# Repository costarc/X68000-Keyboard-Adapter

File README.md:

# X68000 PS/2 Keyboard Adapter (GKA-AT68)

A small adapter that lets a standard PS/2 keyboard drive a Sharp X68000. A PIC16F84 reads the
PS/2 keyboard, translates the scan codes and talks to the X68000 over its 2400 baud keyboard link.

## Repository layout

| Path | What it is |
|---|---|
| `GKA-AT68 Ver1.65 source code (for MPASM).zip` | Original firmware source (PIC assembly, `gkaat68.asm`), Ver1.65 |
| `GKA-AT68 firmware Ver1.65 (INHX8M format for PIC16F84)/` | Original, known-good firmware image (`at68v165.hex`) |
| `GKA-AT68 Assembly Instructions.pdf`, `GKA-AT68 Schematics.png` | Build instructions and schematic |
| `Kicad/` | PCB design (KiCad), fabrication files and interactive BOM |
| `GKA-AT68-C/` | **New:** the firmware rewritten in C for MPLAB X + XC8 (see below) |

## GKA-AT68-C: the C version of the firmware

### Why
The original assembly works, but it is hard to read and hard to change: timing, protocol handling and
key tables are interleaved in one 1,500-line file written for MPASM. The C version exists to give
a firmware that is

- **easier to understand**: one small file per job (PS/2 receive, X68000 UART, key map, main loop);
- **easier to modify**: users can remap keys, change timing or add features without touching assembly;
- **built with a modern toolset**: MPLAB X and the free-mode XC8 compiler (developed with XC8 v2.46).

The assembly version stays in the repository as the reference and the proven firmware. **Its hex is
untouched.** The C version is newer and has been verified by simulation and a compile only, not yet on
hardware (see Status).

### Origin
It is a port of `gkaat68.asm` Ver1.65, not a new design. Kept from the original:

- the hardware and pin roles (PIC16F84 at 9.8304 MHz, PS/2 on RA0-RA3, X68000 link on RB0/RB1/RB3);
- the architecture: a **Timer0 interrupt every ~52 us (1/8 of a 2400 baud bit)** runs a software UART
  for both transmit and receive, with an 8-byte receive FIFO;
- the Timer0 setup and reload constant (`256 - 64 + 3`, prescaler 1:2);
- the PS/2 set-2 to X68000 key tables, transcribed from the assembly.

### Architecture (`GKA-AT68-C/GKA-AT68.X/src`)

| File | Role |
|---|---|
| `main.c` | Port setup and main loop: read PS/2 bytes, handle `E0` (extended) and `F0` (break) prefixes, translate, send to the X68000. Break codes are the make code with bit 7 set. NumLock toggles the LED. |
| `ps2.c` | Blocking PS/2 receiver: one 11-bit frame (start, 8 data LSB first, odd parity, stop), validated for start, parity and stop. |
| `x68k_uart.c` | Timer0 ISR: 2400 baud 8N1 software UART. TX sends a 10-bit frame from a 16-bit shift register; RX centre-samples into a FIFO. TX waits for the host-ready line (RB3). |
| `keymap.c/.h` | `ps2_to_x68_base[]` (index = PS/2 set-2 code), `ps2_to_x68_e0[]` for extended keys, and the NumLock table. `0xFF` = no key. |
| `system.h` | Configuration bits, clock, pin and TRIS definitions. |

### Differences from the assembly
- The C code is a **simpler state machine**, not an instruction-for-instruction translation.
- It only **reads** from the PS/2 keyboard. The assembly's extras are not ported: sending lock-LED
  commands to the keyboard, the 19.2 kbps mode, and host-to-adapter command handling (a stub only).
- PS/2 reception is a plain polling routine in the main loop rather than the assembly's more
  elaborate handling.
- The key tables are the same data, but the C table is indexed directly by the PS/2 code.

### Fixes made after the first port
The first C port had three bugs that each broke the adapter. They are fixed on the branch that
introduced this README:

1. `ps2_read_byte()` waited for 12 clock edges; a PS/2 frame has 11.
2. The UART transmit shift register was 8 bits wide, so bit 7 was lost (every break code arrived as a make).
3. The key table was shifted by one entry.

The original sources are kept in `GKA-AT68-C/GKA-AT68.X/src.orig` for comparison.

### Build
Open `GKA-AT68-C/GKA-AT68.X` in MPLAB X (device PIC16F84A, compiler XC8), or from a shell:

```bash
xc8-cc -mcpu=16F84 -O2 -IGKA-AT68-C/GKA-AT68.X/src GKA-AT68-C/GKA-AT68.X/src/*.c -o at68.elf
```

Result: about 560 of 1024 program words and 40 of 68 data bytes. A prebuilt image is in
`GKA-AT68-C/GKA-AT68.X/at68_xc8_fixed.hex`. If you change the crystal, update `_XTAL_FREQ` in
`system.h` and the Timer0 reload in `x68k_uart.c`.

### Verification and status
`GKA-AT68-C/tests/gka-verify-fixed.py` simulates the transmit routine, the PS/2 receiver and the key
table (run `python -I GKA-AT68-C/tests/gka-verify-fixed.py GKA-AT68-C/GKA-AT68.X/src`). It checks that all
256 bytes transmit with valid framing, that PS/2 frames are received exactly, and that 73 of 73 reference keys map correctly.
It does not model real interrupt latency or clock timing.

**Not yet verified on hardware.** Before relying on it, check: the TX line (RB1) shows about 416.7 us per
bit (2400 baud); keys and releases register on the X68000 with none stuck; keypad and function keys
map correctly; the NumLock LED follows the key.

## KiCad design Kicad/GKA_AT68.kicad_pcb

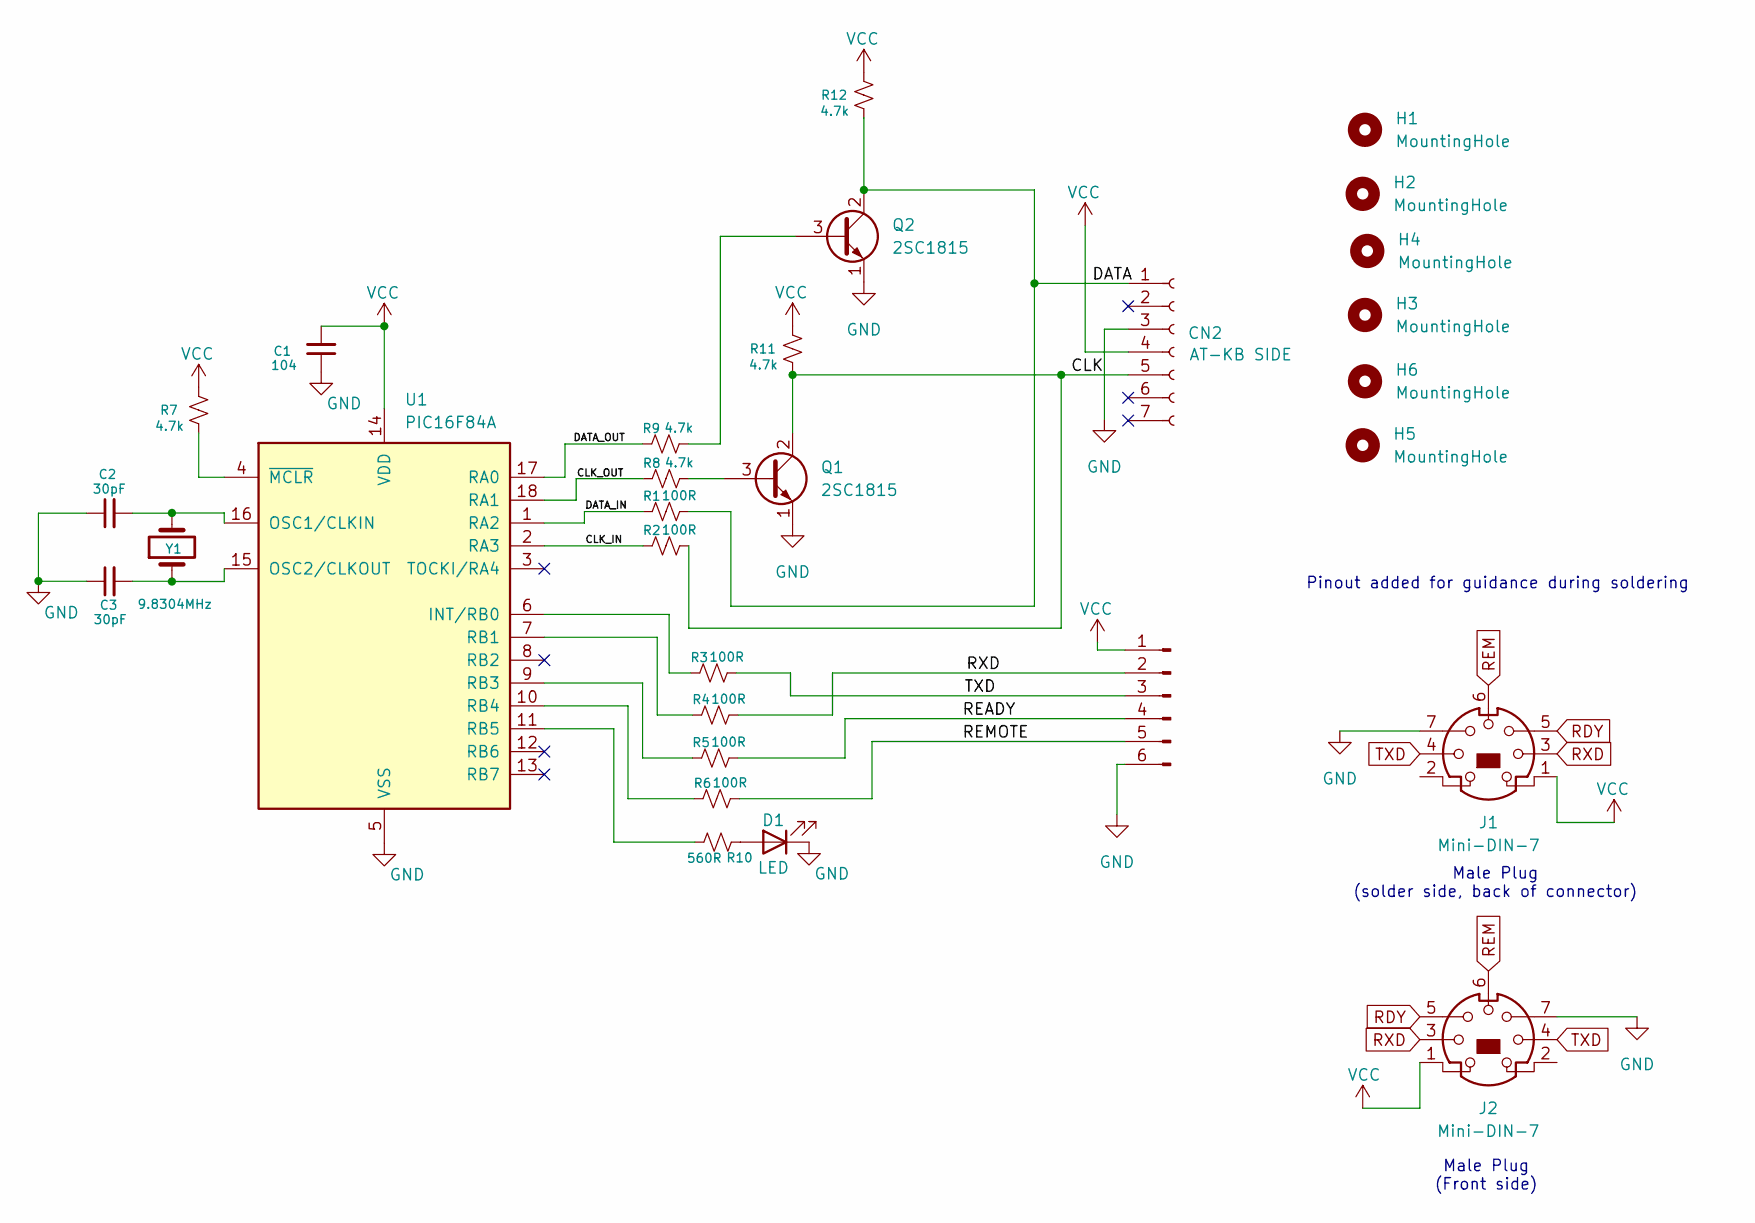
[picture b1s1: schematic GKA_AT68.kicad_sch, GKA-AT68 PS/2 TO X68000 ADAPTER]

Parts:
C1: 104; C_Disc_D5.0mm_W2.5mm_P5.00mm
C2, C3: 30pF; C_Disc_D5.0mm_W2.5mm_P5.00mm
CN1: X68000 Keyboard; SolderWire-0.5sqmm_1x06_P4.6mm_D0.9mm_OD2.1mm
CN2: AT-KB SIDE; MINI-DIN-6-FULL-SHIELD
D1: LED; LED_D3.0mm
H1, H2, H3, H4, H5, H6: MountingHole; MountingHole_2.1mm
J1, J2: Mini-DIN-7
Q1, Q2: 2SC1815; TO-92_HandSolder
R1, R2, R3, R4, R5, R6: 100R; R_Axial_DIN0207_L6.3mm_D2.5mm_P7.62mm_Horizontal
R7, R8, R9, R11, R12: 4.7k; R_Axial_DIN0207_L6.3mm_D2.5mm_P7.62mm_Horizontal
R10: 560R; R_Axial_DIN0207_L6.3mm_D2.5mm_P7.62mm_Horizontal
U1: PIC16F84A; DIP-18_W7.62mm_Socket
Y1: 9.8304MHz; Crystal_HC49-U_Vertical

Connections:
/CLK: CN2.5, Q1.2 (C), R2.2, R11.1
/CLK_IN: R2.1, U1.2 (RA3)
/CLK_OUT: R8.1, U1.18 (RA1)
/DATA: CN2.1, Q2.2 (C), R1.2, R12.1
/DATA_IN: R1.1, U1.1 (RA2)
/DATA_OUT: R9.1, U1.17 (RA0)
/READY: CN1.4, R5.2
/REMOTE: CN1.5, R6.2
GND: C1.1, C2.1, C3.1, CN1.6, CN2.3, D1.1 (K), J1.7, J2.7, Q1.1 (E), Q2.1 (E), U1.5 (VSS)
unnamed: D1.2 (A), R10.1
unnamed: J1.3, J2.3
unnamed: J1.4, J2.4
unnamed: J1.5, J2.5
unnamed: J1.6, J2.6
unnamed: Q1.3 (B), R8.2
unnamed: Q2.3 (B), R9.2
unnamed: R3.1, U1.6 (INT/RB0)
unnamed: C2.2, U1.16 (OSC1/CLKIN), Y1.2
unnamed: C3.2, U1.15 (OSC2/CLKOUT), Y1.1
unnamed: R4.1, U1.7 (RB1)
unnamed: R5.1, U1.9 (RB3)
unnamed: R6.1, U1.10 (RB4)
unnamed: R10.2, U1.11 (RB5)
unnamed: R7.1, U1.4 (~MCLR)
RXD: CN1.2, R4.2
TXD: CN1.3, R3.2
VCC: C1.2, CN1.1, CN2.4, J1.1, J2.1, R7.2, R11.2, R12.2, U1.14 (VDD)

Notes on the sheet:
Pinout added for guidance during soldering
Male Plug (solder side, back of connector)
Male Plug (Front side)

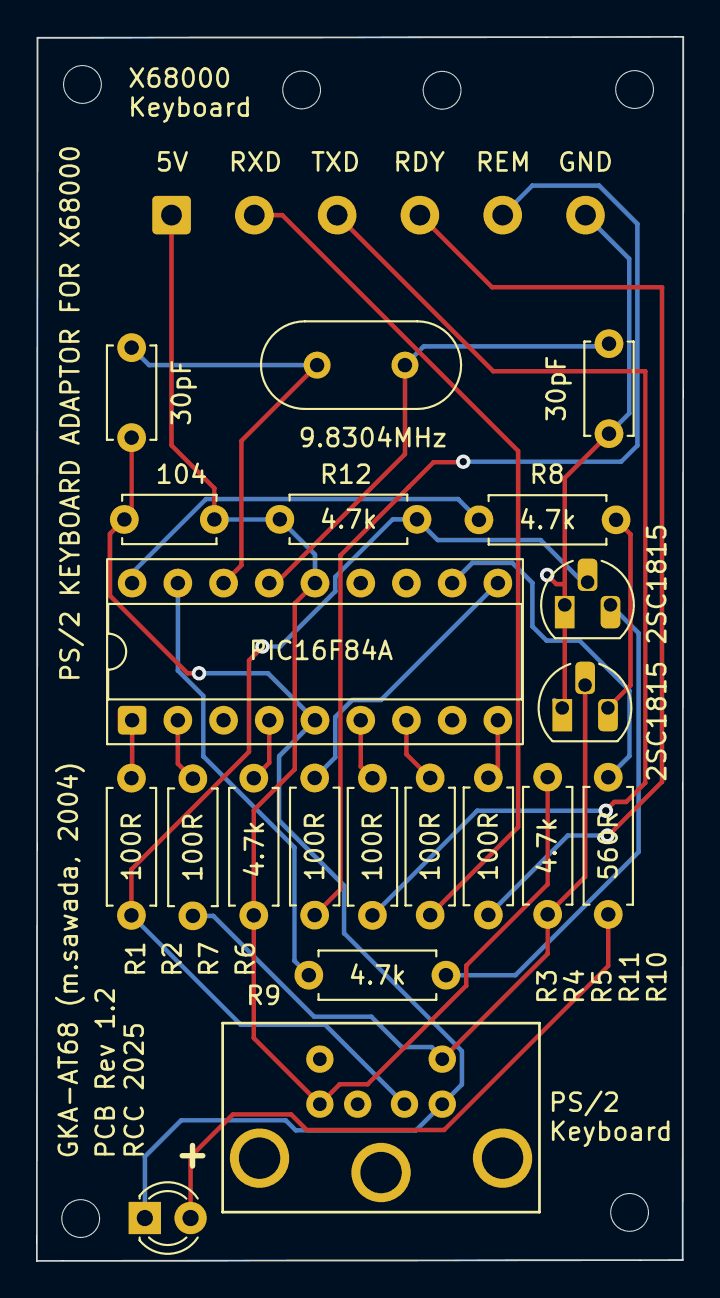
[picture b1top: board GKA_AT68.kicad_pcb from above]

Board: 2 copper layers, 35.9 x 68.0 mm, 28 parts (0 on the bottom side), 23 nets.

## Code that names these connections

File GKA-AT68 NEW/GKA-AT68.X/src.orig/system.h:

#ifndef SYSTEM_H
#define SYSTEM_H

#include <xc.h>
#include <stdint.h>
#include <stdbool.h>

// Configure for HS oscillator @ 9.8304 MHz
#define _XTAL_FREQ 9830400UL

// CONFIG (XC8 v2+ syntax)
#pragma config FOSC = HS        // HS oscillator
#pragma config WDTE = OFF       // Watchdog Timer disabled
#pragma config PWRTE = ON       // Power-up Timer enabled
#pragma config CP   = OFF       // Code protection disabled

// Port bit helpers (read/writes to PORT bits)
#define PS2_DATA_DRV   RA0
#define PS2_CLK_DRV    RA1
#define PS2_DATA_IN    RA2
#define PS2_CLK_IN     RA3

#define HOST_RX        RB0
#define HOST_TX        RB1
#define HOST_RDY       RB3
#define HOST_REMOTE    RB4
#define LED            RB5

// TRIS configuration
#define TRISA_MASK  0b00001100  // RA2,RA3 inputs; RA0,RA1 outputs
#define TRISB_MASK  0b00001001  // RB3,RB0 inputs; RB1,RB4,RB5 outputs

#endif

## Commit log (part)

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2024-09-07 Rev 1.1
2024-09-07 Added IBOM
2025-06-07 Added component values to pcb / silk
